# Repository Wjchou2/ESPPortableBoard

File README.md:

# ESPPortableBoard

<br>
<br>
A portable devboard designed to be a small customizable gadget. It includes 3 Buttons, a 0.91 inch OLED screen and is power by an ESPRESSIF ESP32-WROOM-32E-N4. 
Power is from a usb port.

This project was originally meant to be a mini mp4 player, but it can also be customized, the buttons used for control and the small screen for display. 

Other Features:
- Power indicator LEDS
- Boot/RST Buttons
- USB-C Powered
- Micro SD Card slot for audio, image, data storage.

[See Kicanvas Link Here!
](https://kicanvas.org/?repo=https%3A%2F%2Fgithub.com%2FWjchou2%2FESPPortableBoard%2Ftree%2Fmain%2Fkicad)

# Schematic

# PCB

# Case

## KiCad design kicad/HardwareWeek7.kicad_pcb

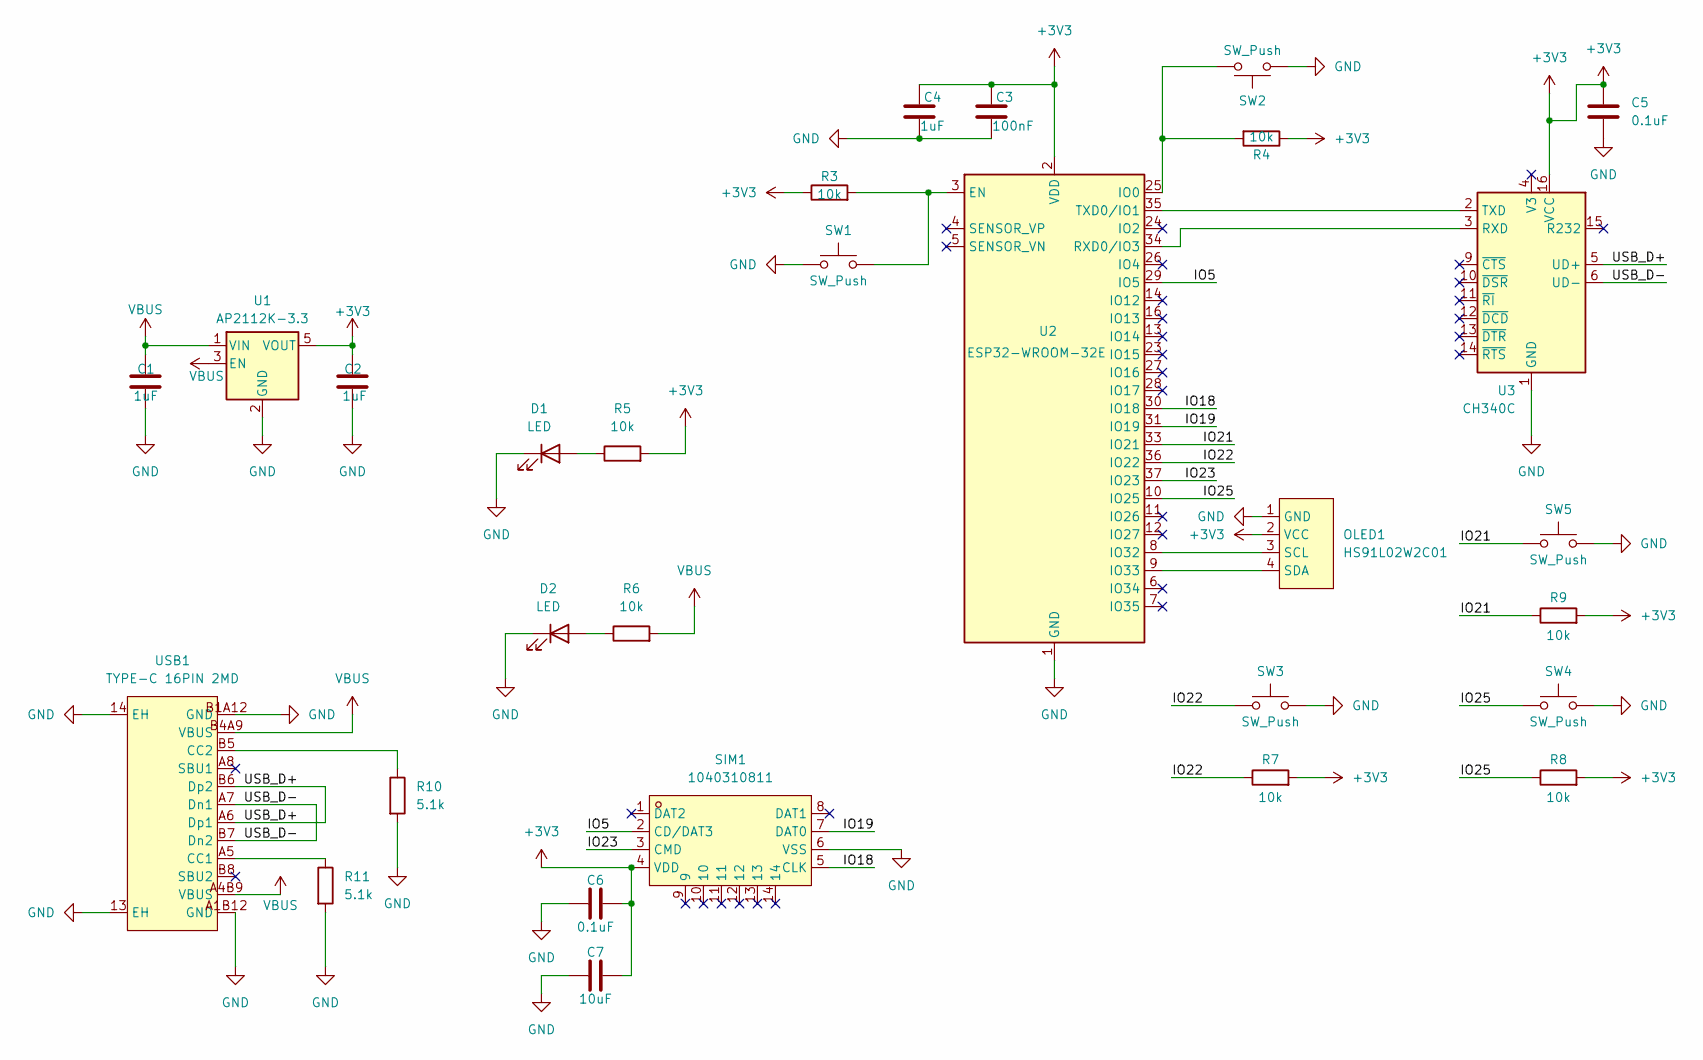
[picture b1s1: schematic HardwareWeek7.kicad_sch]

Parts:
C1, C2, C4: 1uF; C_0603_1608Metric; LCSC Part C29936
C3: 100nF; C_0603_1608Metric; LCSC Part C14663
C5, C6: 0.1uF; C_0603_1608Metric; LCSC Part C14663
C7: 10uF; C_0603_1608Metric; LCSC Part C96446
D1, D2: LED; LED_0603_1608Metric; LCSC Part C19171390
OLED1: HS91L02W2C01; OLED-TH_L38.0-W12.0_HS91L02W2C01; MPN HS91L02W2C01; LCSC Part C5248081
R3, R4, R5, R6, R7, R8, R9: 10k; R_0603_1608Metric; LCSC Part C2906982
R10, R11: 5.1k; R_0603_1608Metric; LCSC Part C2907044
SIM1: 1040310811; SIM-SMD_8P-1040310811; MPN 1040310811; LCSC Part C585350
SW1, SW2: SW_Push; KEY-SMD_L4.0-W3.0-LS4.9-1; LCSC Part C49234124
SW3, SW4, SW5: SW_Push; SW-SMD_SH-6X6X4.5H-TP; LCSC Part C42416254
U1: AP2112K-3.3; SOT-23-5; LCSC Part C51118
U2: ESP32-WROOM-32E; LCSC Part C701341
U3: CH340C; SOIC-16_3.9x9.9mm_P1.27mm; LCSC Part C84681
USB1: TYPE-C 16PIN 2MD; USB-C-SMD_TYPE-C-16PIN-2MD-073; MPN TYPE-C 16PIN 2MD(073); LCSC Part C2765186

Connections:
+3V3: C2.1, C3.2, C4.2, C5.1, C6.2, C7.2, OLED1.2 (VCC), R3.1, R4.1, R5.2, R7.2, R8.2, R9.2, SIM1.4 (VDD), U1.5 (VOUT), U2.2 (VDD), U3.16 (VCC)
/IO5: SIM1.2 (CD/DAT3), U2.29 (IO5)
/IO18: SIM1.5 (CLK), U2.30 (IO18)
/IO19: SIM1.7 (DAT0), U2.31 (IO19)
/IO21: R9.1, SW5.1, U2.33 (IO21)
/IO22: R7.1, SW3.1, U2.36 (IO22)
/IO23: SIM1.3 (CMD), U2.37 (IO23)
/IO25: R8.1, SW4.1, U2.10 (IO25)
/USB_D+: U3.5 (UD+), USB1.A6 (Dp1), USB1.B6 (Dp2)
/USB_D-: U3.6 (UD-), USB1.A7 (Dn1), USB1.B7 (Dn2)
GND: C1.2, C2.2, C3.1, C4.1, C5.2, C6.1, C7.1, D1.1 (K), D2.1 (K), OLED1.1 (GND), R10.2, R11.2, SIM1.6 (VSS), SW1.1, SW2.1, SW3.2, SW4.2, SW5.2, U1.2 (GND), U2.1 (GND), U2.15 (GND), U2.38 (GND), U2.39 (GND), U3.1 (GND), USB1.13 (EH), USB1.14 (EH), USB1.A1B12 (GND), USB1.B1A12 (GND)
unnamed: D1.2 (A), R5.1
unnamed: D2.2 (A), R6.1
unnamed: OLED1.3 (SCL), U2.8 (IO32)
unnamed: OLED1.4 (SDA), U2.9 (IO33)
unnamed: R3.2, SW1.2, U2.3 (EN)
unnamed: R4.2, SW2.2, U2.25 (IO0)
unnamed: U2.34 (RXD0/IO3), U3.3 (RXD)
unnamed: U2.35 (TXD0/IO1), U3.2 (TXD)
unnamed: R11.1, USB1.A5 (CC1)
unnamed: R10.1, USB1.B5 (CC2)
VBUS: C1.1, R6.2, U1.1 (VIN), U1.3 (EN), USB1.A4B9 (VBUS), USB1.B4A9 (VBUS)

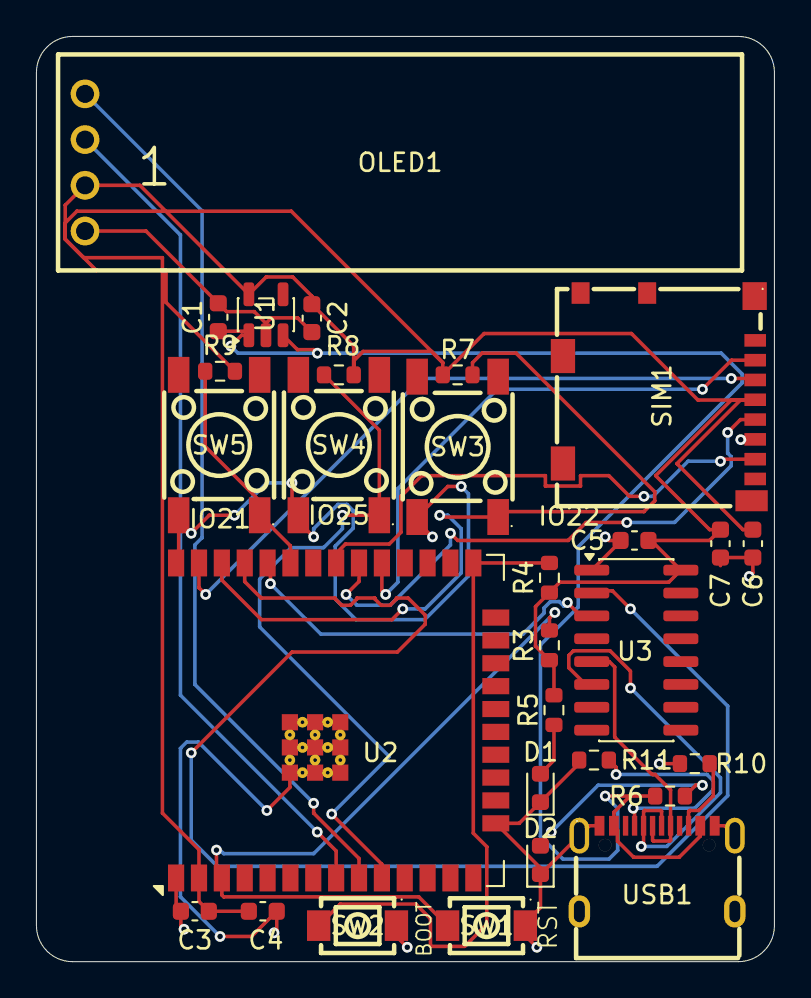
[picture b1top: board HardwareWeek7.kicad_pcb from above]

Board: 2 copper layers, 41.0 x 51.4 mm, 29 parts (0 on the bottom side), 22 nets.

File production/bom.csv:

Designator,Footprint,Quantity,Value,LCSC Part #
"C1, C2, C4",0603,3,1uF,
C3,0603,1,100nF,
"C5, C6",0603,2,0.1uF,
C7,0603,1,10uF,
"D1, D2",0603,2,LED,
OLED1,OLED-TH_L38.0-W12.0_HS91L02W2C01,1,HS91L02W2C01,C5248081
"R10, R11",0603,2,5.1k,
"R3, R4, R5, R6, R7, R8, R9",0603,7,10k,
SIM1,SIM-SMD_8P-1040310811,1,1040310811,C585350
"SW1, SW2",KEY-SMD_L4.0-W3.0-LS4.9-1,2,SW_Push,C49234124
"SW3, SW4, SW5",SW-SMD_SH-6X6X4.5H-TP,3,SW_Push,C42416254
U1,SOT-23-5,1,AP2112K-3.3,
U2,ESP32-WROOM-32E,1,ESP32-WROOM-32E,
U3,SOIC-16_3.9x9.9mm_P1.27mm,1,CH340C,
USB1,USB-C-SMD_TYPE-C-16PIN-2MD-073,1,TYPE-C 16PIN 2MD,C2765186
